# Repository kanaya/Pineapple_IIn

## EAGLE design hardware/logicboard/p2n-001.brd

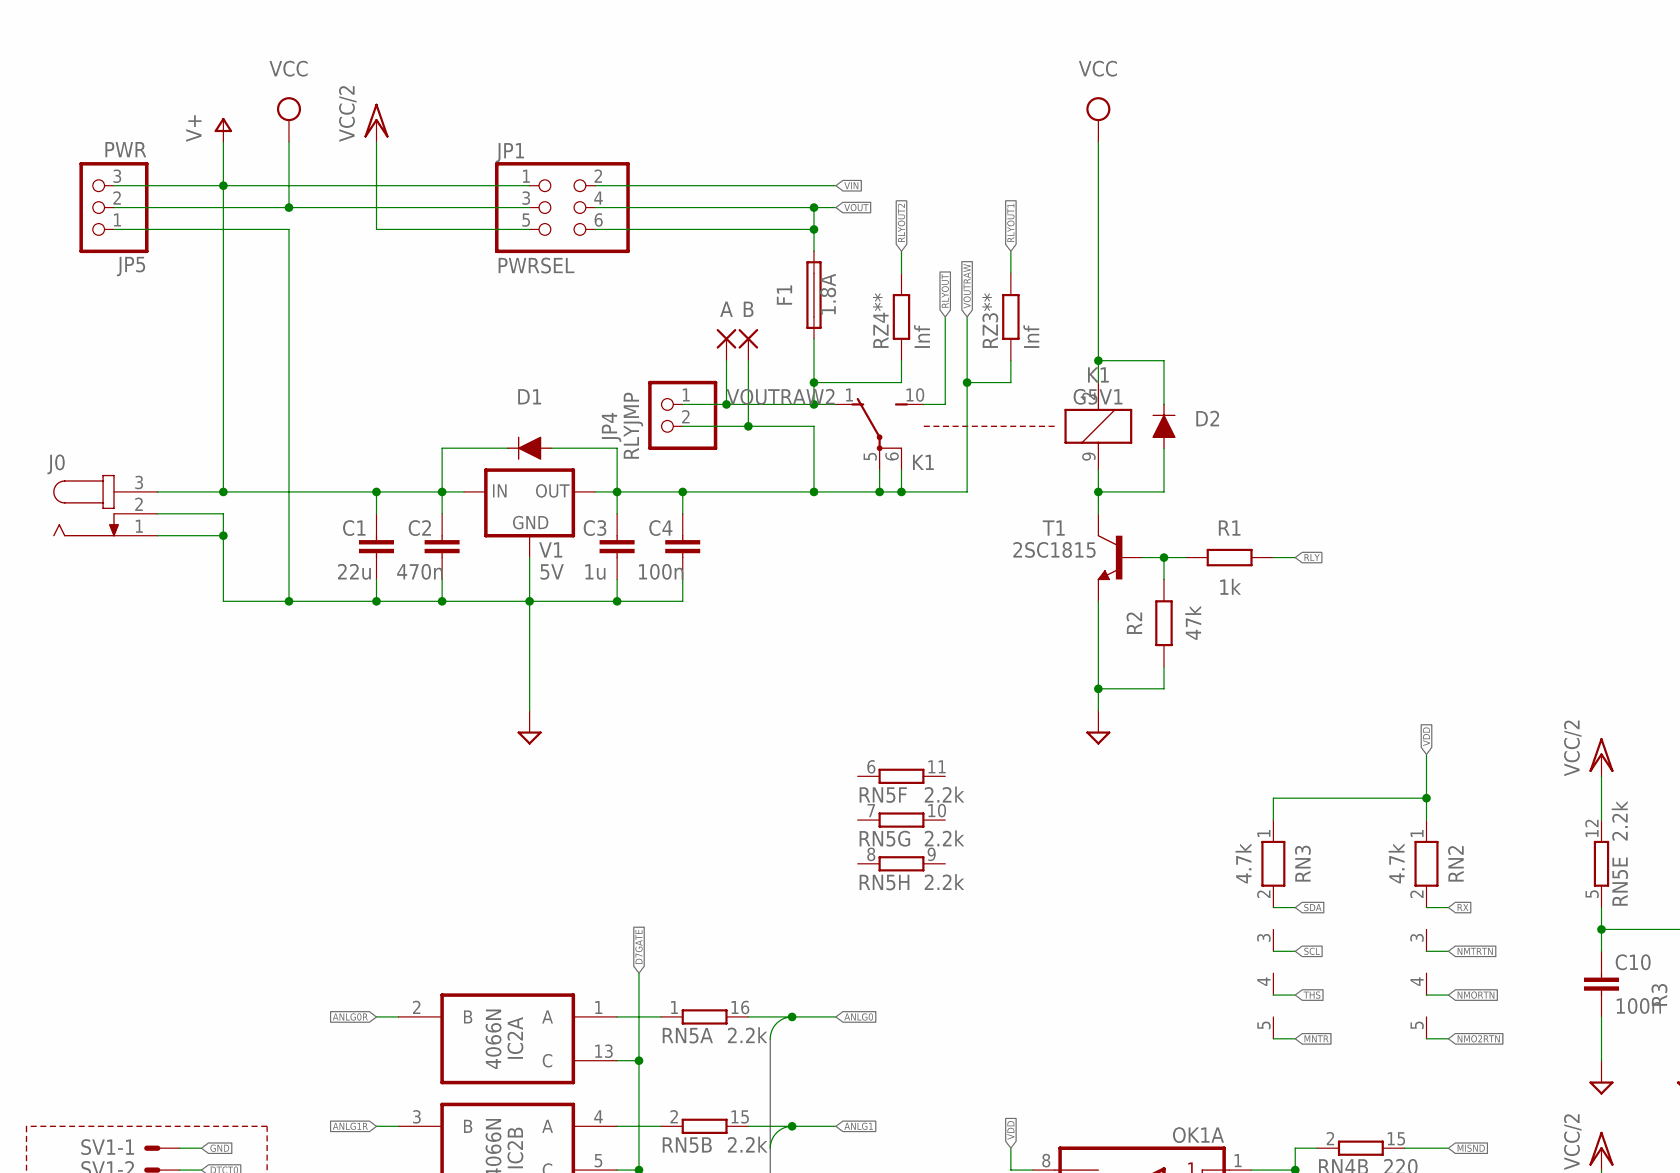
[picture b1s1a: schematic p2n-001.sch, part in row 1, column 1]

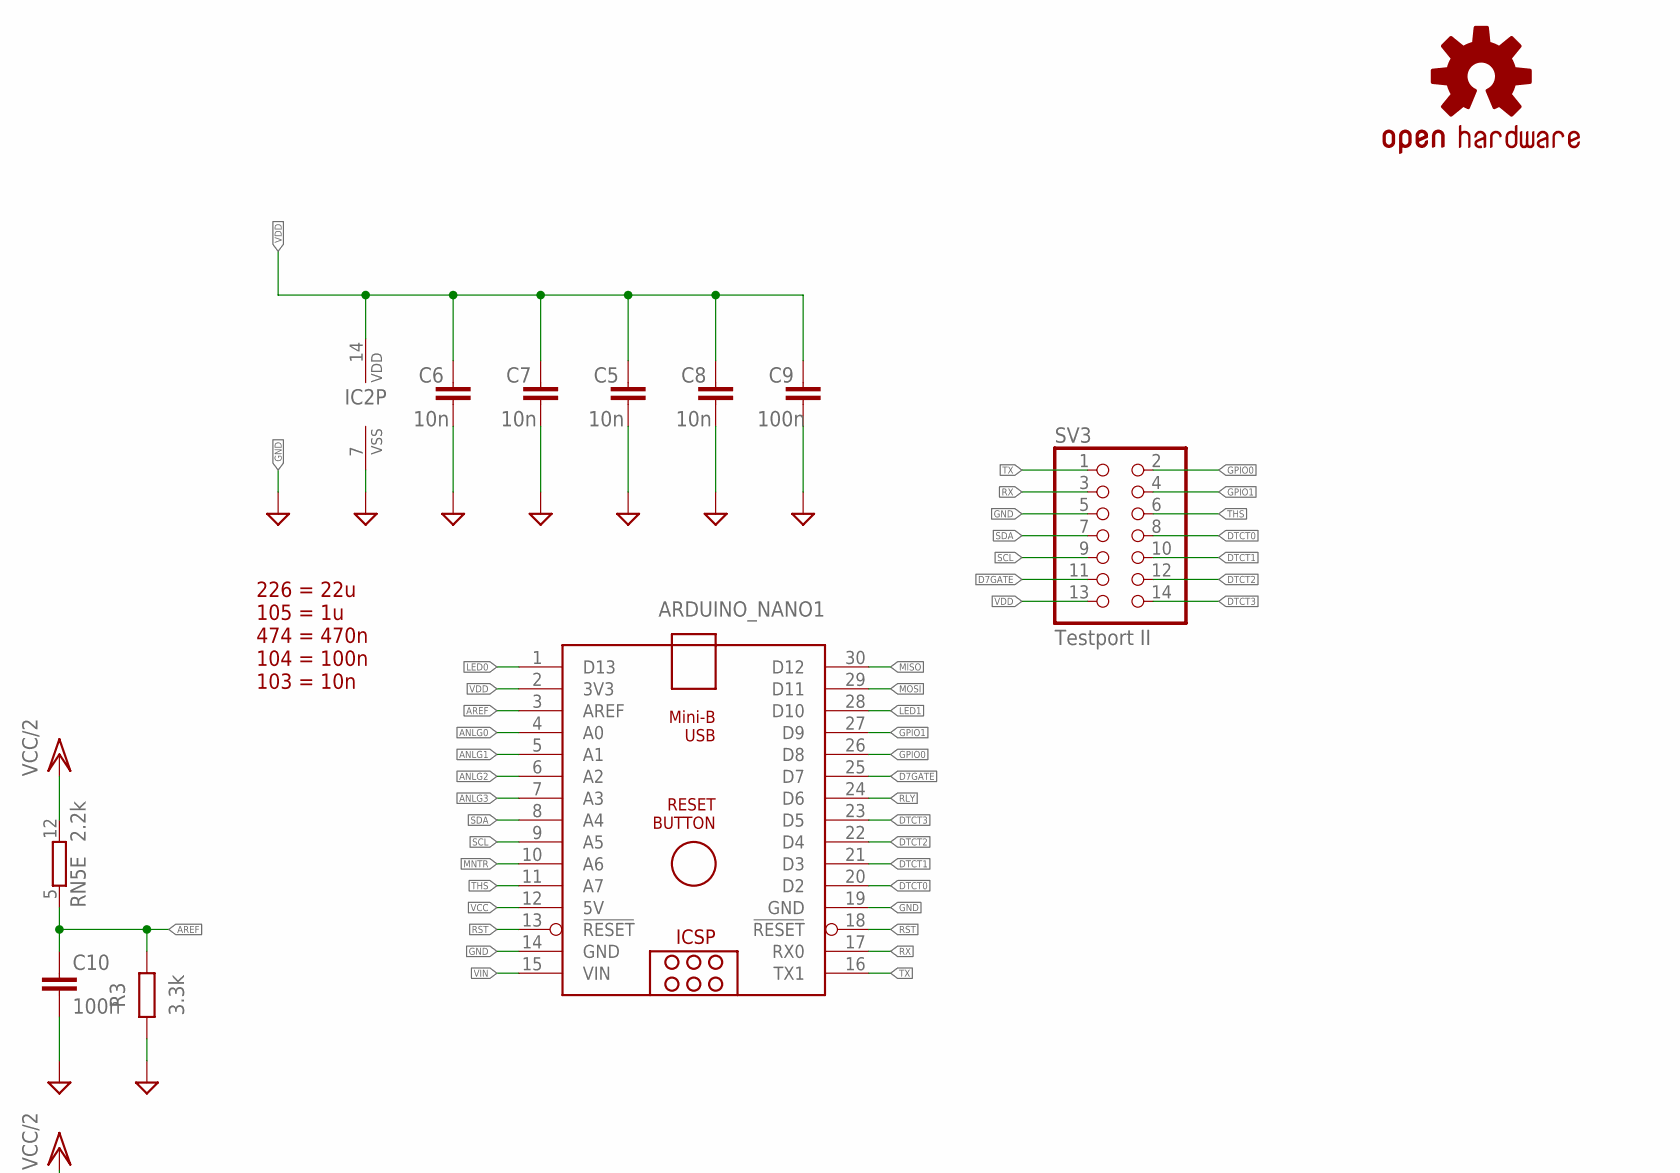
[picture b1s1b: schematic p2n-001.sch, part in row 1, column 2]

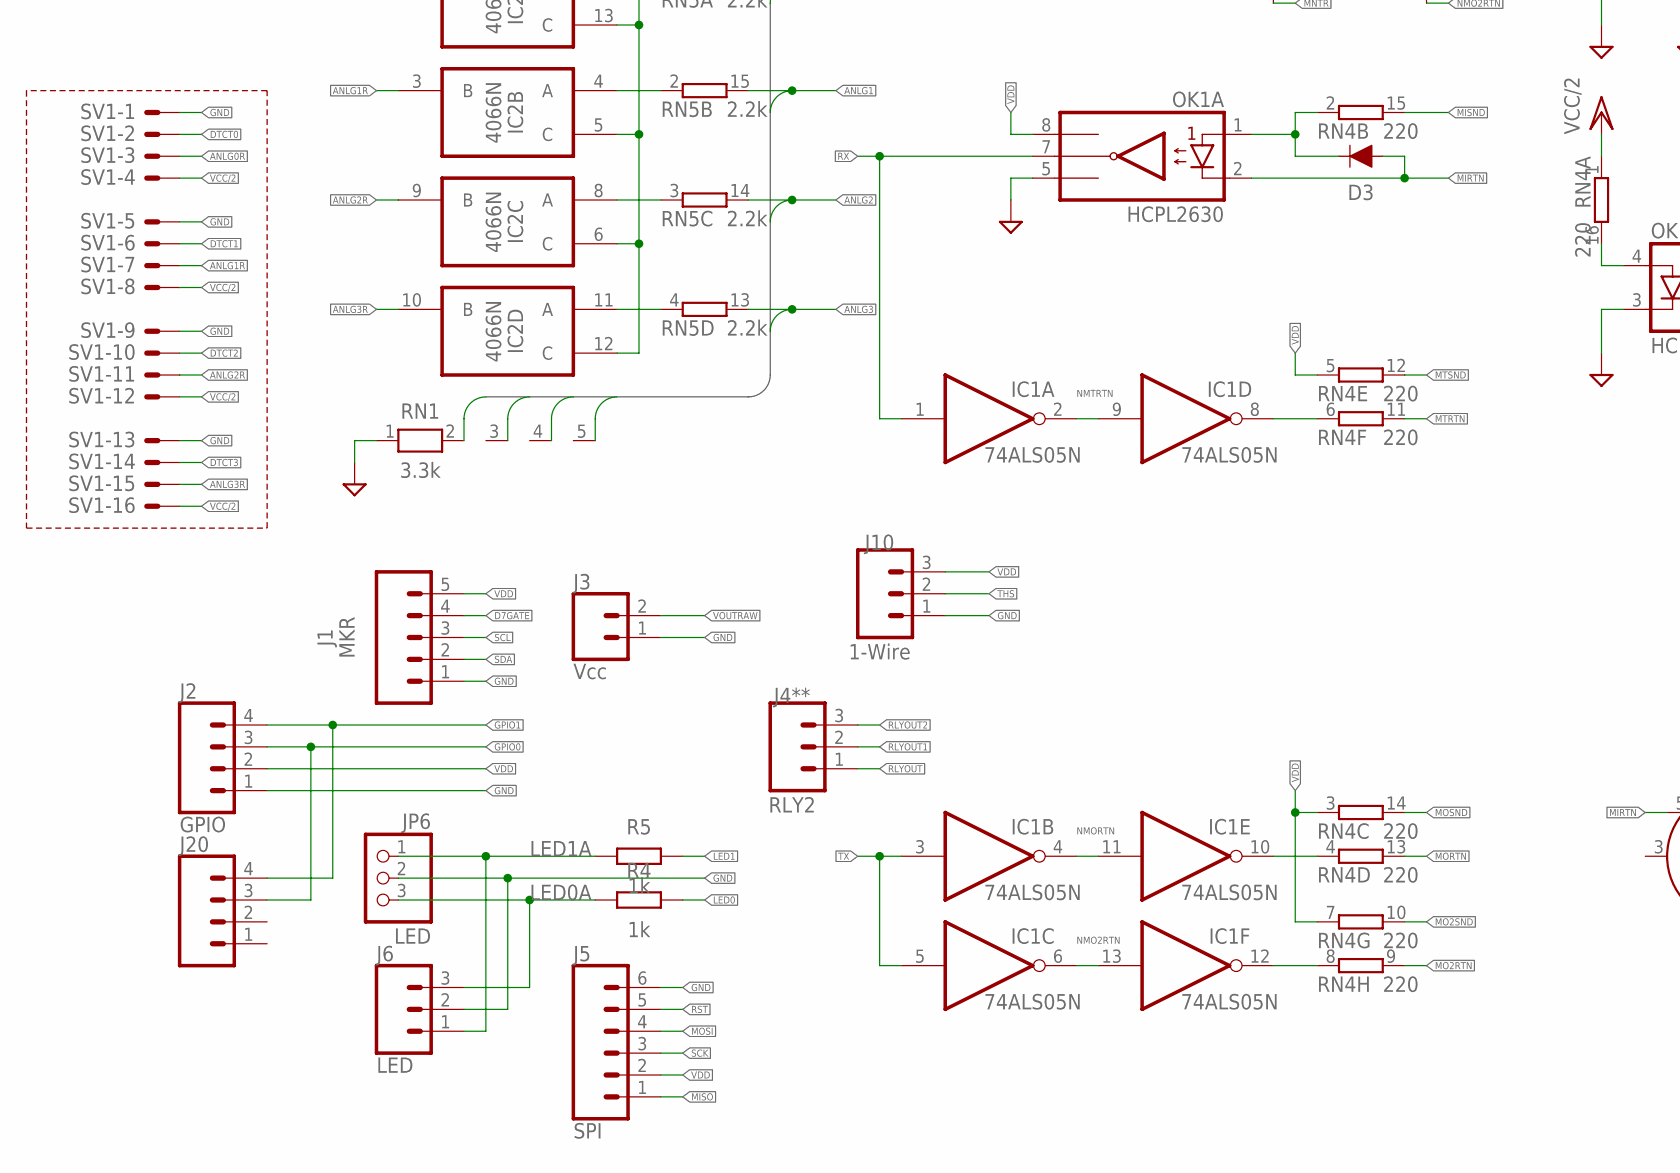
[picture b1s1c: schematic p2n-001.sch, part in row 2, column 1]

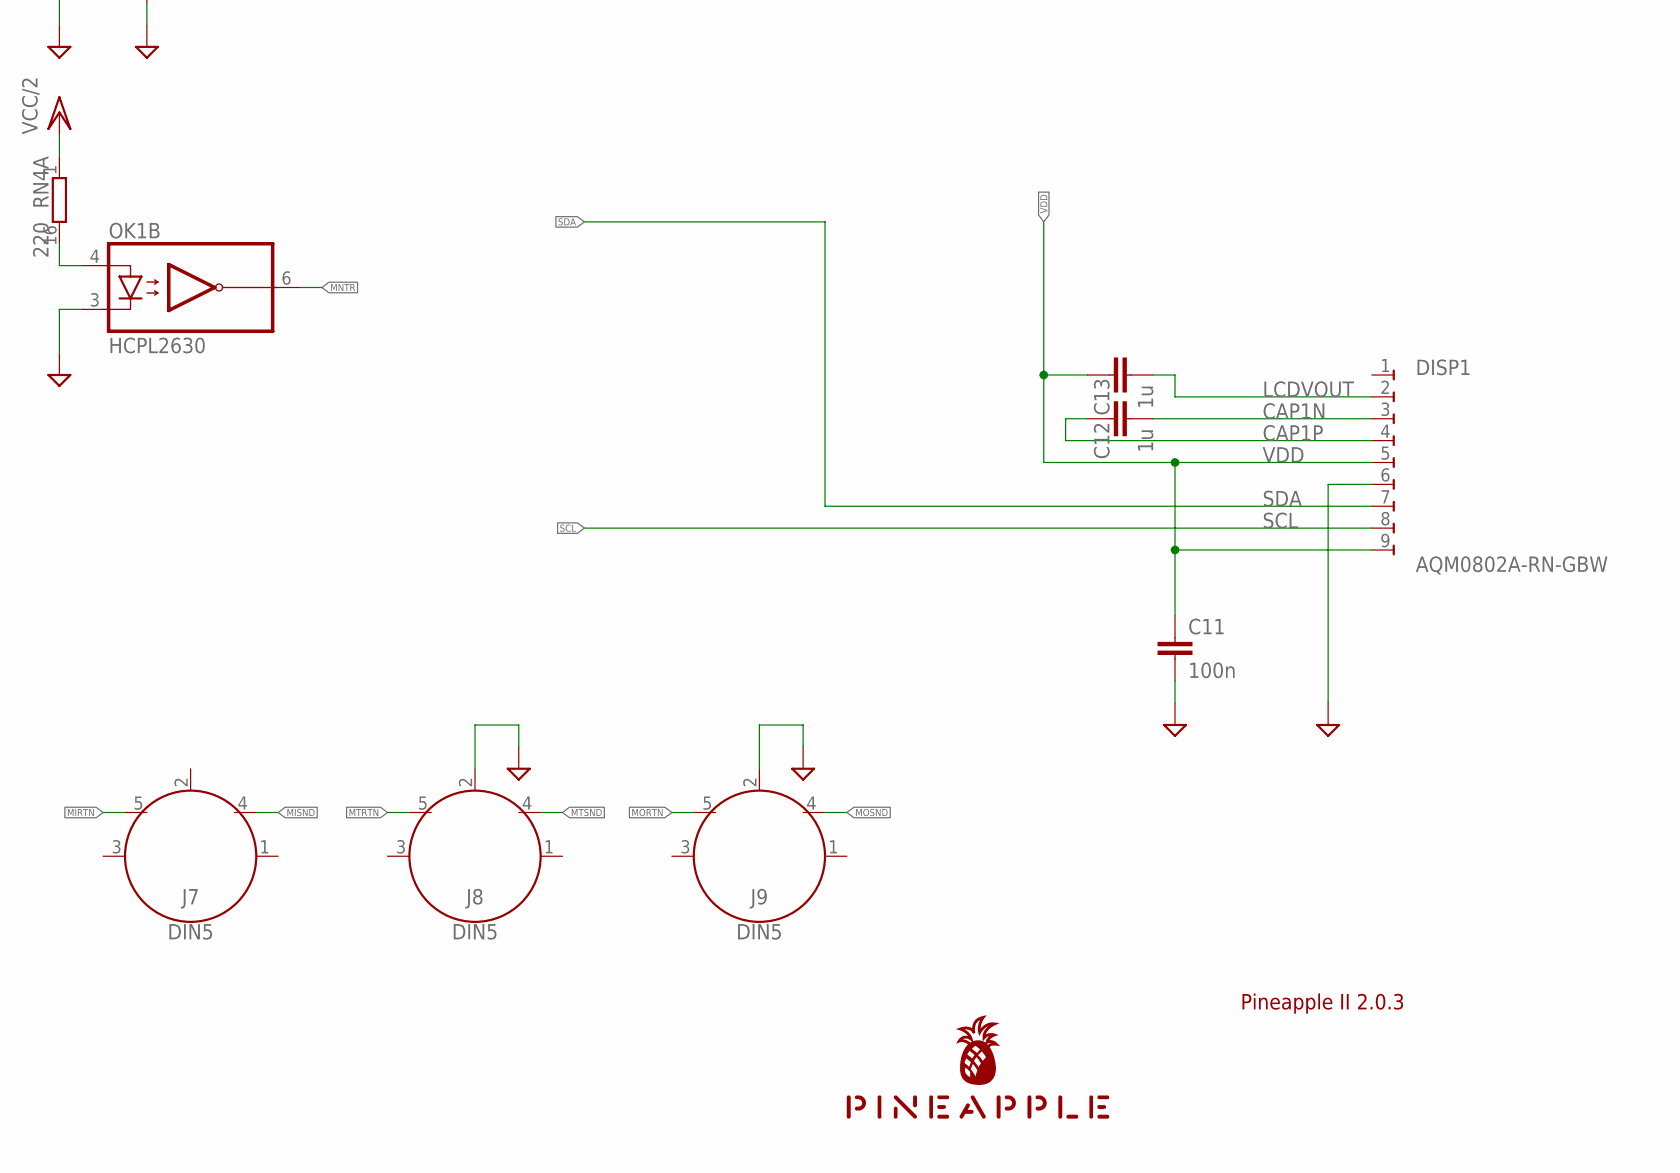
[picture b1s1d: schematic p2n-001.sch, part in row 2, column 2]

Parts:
A: SMD2; SMD1,27-2,54
ARDUINO_NANO1: ARDUINO_NANO
B: SMD2; SMD1,27-2,54
C1: 22u; C025-050X050
C2: 470n; C050-024X044
C3, C12, C13: 1u; C050-024X044
C4, C9, C10, C11: 100n; C025-024X044
C5, C6, C7, C8: 10n; C025-024X044
D1, D2, D3: DIODE-1N4148
DISP1: AQM0802A-RN-GBW; AQM0802A-RN-GBW-FOOTPRINT
F1: 1.8A; TE5
IC1: 74ALS05N; DIL14
IC2: 4066N; DIL14
J0: JACK-PLUG0; SPC4077
J1: MKR; JST-5-PTH
J2: GPIO; JST-4-PTH
J3: Vcc; JST-2-PTH
J4**: RLY2; JST-3-PTH-NS
J5: SPI; 1X06_1.27MM
J6: LED; JST-3-PTH-VERT
J7, J8, J9: DIN5; DIN5-RA-PTH
J10: 1-Wire; JST-3-PTH-VERT
J20: CONN_041.27MM; 1X04_1.27MM
JP1: PWRSEL; 2X03
JP4: RLYJMP; 1X02
JP5: PWR; 1X03
JP6: LED; 1X03
K1: G5V1
LOGO1: OSHW-LOGOS-COPPER; OSHW-LOGO-S_COPPER
OK1: HCPL2630; DIL08
R1, R4, R5: 1k; 0204/5
R2: 47k; 0204/5
R3: 3.3k; 0204/5
RN1: 3.3k; RN-5
RN2, RN3: 4.7k; RN-5
RN4: 220; DIL16
RN5: 2.2k; DIL16
RZ3**, RZ4**: Inf; M2012
SV1: ML16LE; ML16L
SV3: Testport II; 2X07
T1: 2SC1815; TO92-ECB
U$1: PINEAPPLE450_SILK
V1: 5V; 78XXL

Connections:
ANLG0: ARDUINO_NANO1.4 (A0), RN1.2, RN5.16 (2)
ANLG0R: IC2.2 (B), SV1.3
ANLG1: ARDUINO_NANO1.5 (A1), RN1.3, RN5.15 (2)
ANLG1R: IC2.3 (B), SV1.7
ANLG2: ARDUINO_NANO1.6 (A2), RN1.4, RN5.14 (2)
ANLG2R: IC2.9 (B), SV1.11
ANLG3: ARDUINO_NANO1.7 (A3), RN1.5, RN5.13 (2)
ANLG3R: IC2.10 (B), SV1.15
AREF: ARDUINO_NANO1.3 (AREF), C10.1, R3.2, RN5.5 (1)
CAP1N: C12.2, DISP1.3
CAP1P: C12.1, DISP1.4
D7GATE: ARDUINO_NANO1.25 (D7), IC2.5 (C), IC2.6 (C), IC2.12 (C), IC2.13 (C), J1.4, SV3.11
DTCT0: ARDUINO_NANO1.20 (D2), SV1.2, SV3.8
DTCT1: ARDUINO_NANO1.21 (D3), SV1.6, SV3.10
DTCT2: ARDUINO_NANO1.22 (D4), SV1.10, SV3.12
DTCT3: ARDUINO_NANO1.23 (D5), SV1.14, SV3.14
GND: ARDUINO_NANO1.14 (GND), ARDUINO_NANO1.19 (GND), C1.2, C2.2, C3.2, C4.2, C5.2, C6.2, C7.2, C8.2, C9.2, C10.2, C11.2, DISP1.6, IC1.7 (GND), IC2.7 (VSS), J0.1, J0.2, J1.1, J2.1, J3.1, J5.6, J6.2, J8.2, J9.2, J10.1, JP5.1, JP6.2, OK1.3 (C2), OK1.5 (GND), R2.1, R3.1, RN1.1, SV1.1, SV1.5, SV1.9, SV1.13, SV3.5, T1.E, V1.GND
GPIO0: ARDUINO_NANO1.26 (D8), J2.3, J20.3, SV3.2
GPIO1: ARDUINO_NANO1.27 (D9), J2.4, J20.4, SV3.4
LCDVOUT: C13.2, DISP1.2
LED0: ARDUINO_NANO1.1 (D13), R4.2
LED0A: J6.3, JP6.3, R4.1
LED1: ARDUINO_NANO1.28 (D10), R5.2
LED1A: J6.1, JP6.1, R5.1
MIDIINSND: D3.C, OK1.1 (A1), RN4.2 (1)
MIRTN: D3.A, J7.5, OK1.2 (C1)
MISND: J7.4, RN4.15 (2)
MISO: ARDUINO_NANO1.30 (D12), J5.1
MNTR: ARDUINO_NANO1.10 (A6), OK1.6 (VO2), RN3.5
MNTRA: OK1.4 (A2), RN4.16 (2)
MO2RTN: RN4.9 (2)
MO2RTNRAW: IC1.12 (O), RN4.8 (1)
MO2SND: RN4.10 (2)
MORTN: J9.5, RN4.13 (2)
MORTNRAW: IC1.10 (O), RN4.4 (1)
MOSI: ARDUINO_NANO1.29 (D11), J5.4
MOSND: J9.4, RN4.14 (2)
MTRTN: J8.5, RN4.11 (2)
MTRTNRAW: IC1.8 (O), RN4.6 (1)
MTSND: J8.4, RN4.12 (2)
unnamed: IC2.1 (A), RN5.1
unnamed: IC2.4 (A), RN5.2 (1)
unnamed: IC2.8 (A), RN5.3 (1)
unnamed: IC2.11 (A), RN5.4 (1)
NMO2RTN: IC1.6 (O), IC1.13 (I), RN2.5
NMORTN: IC1.4 (O), IC1.11 (I), RN2.4
NMTRTN: IC1.2 (O), IC1.9 (I), RN2.3
RLY: ARDUINO_NANO1.24 (D6), R1.2
RLYDRV: R1.1, R2.2, T1.B
RLYOUT: J4**.1, K1.10 (S)
RLYOUT1: J4**.2, RZ3**.2
RLYOUT2: J4**.3, RZ4**.2
RLYSNK: D2.A, K1.9 (2), T1.C
RST: ARDUINO_NANO1.13 (!RESET), ARDUINO_NANO1.18 (!RESET), J5.5
RX: ARDUINO_NANO1.17 (RX0), IC1.1 (I), OK1.7 (VO1), RN2.2, SV3.3
SCK: J5.3
SCL: ARDUINO_NANO1.9 (A5), DISP1.8, J1.3, RN3.3, SV3.9
SDA: ARDUINO_NANO1.8 (A4), DISP1.7, J1.2, RN3.2, SV3.7
THS: ARDUINO_NANO1.11 (A7), J10.2, RN3.4, SV3.6
TX: ARDUINO_NANO1.16 (TX1), IC1.3 (I), IC1.5 (I), SV3.1
V+: C1.1, C2.1, D1.C, J0.3, JP1.1, JP5.3, V1.IN
VCC: ARDUINO_NANO1.12 (5V), D2.C, IC1.14 (VCC), JP1.3, JP5.2, K1.2 (1)
VCC/2: JP1.5, RN4.1, RN5.12 (2), SV1.4, SV1.8, SV1.12, SV1.16
VDD: ARDUINO_NANO1.2 (3V3), C5.1, C6.1, C7.1, C8.1, C9.1, C11.1, C13.1, DISP1.5, DISP1.9, IC2.14 (VDD), J1.5, J2.2, J5.2, J10.3, OK1.8 (VCC), RN2.1, RN3.1, RN4.3 (1), RN4.5 (1), RN4.7 (1), SV3.13
VIN: ARDUINO_NANO1.15 (VIN), JP1.2
VOUT: F1.2, JP1.4, JP1.6
VOUTRAW: B.1, C3.1, C4.1, D1.A, J3.2, JP4.2, K1.5, K1.6, RZ3**.1, V1.OUT
VOUTRAW2: A.1, F1.1, JP4.1, K1.1 (O), RZ4**.1

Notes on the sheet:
Pineapple II 2.0.3
226 = 22u 105 = 1u 474 = 470n 104 = 100n 103 = 10n

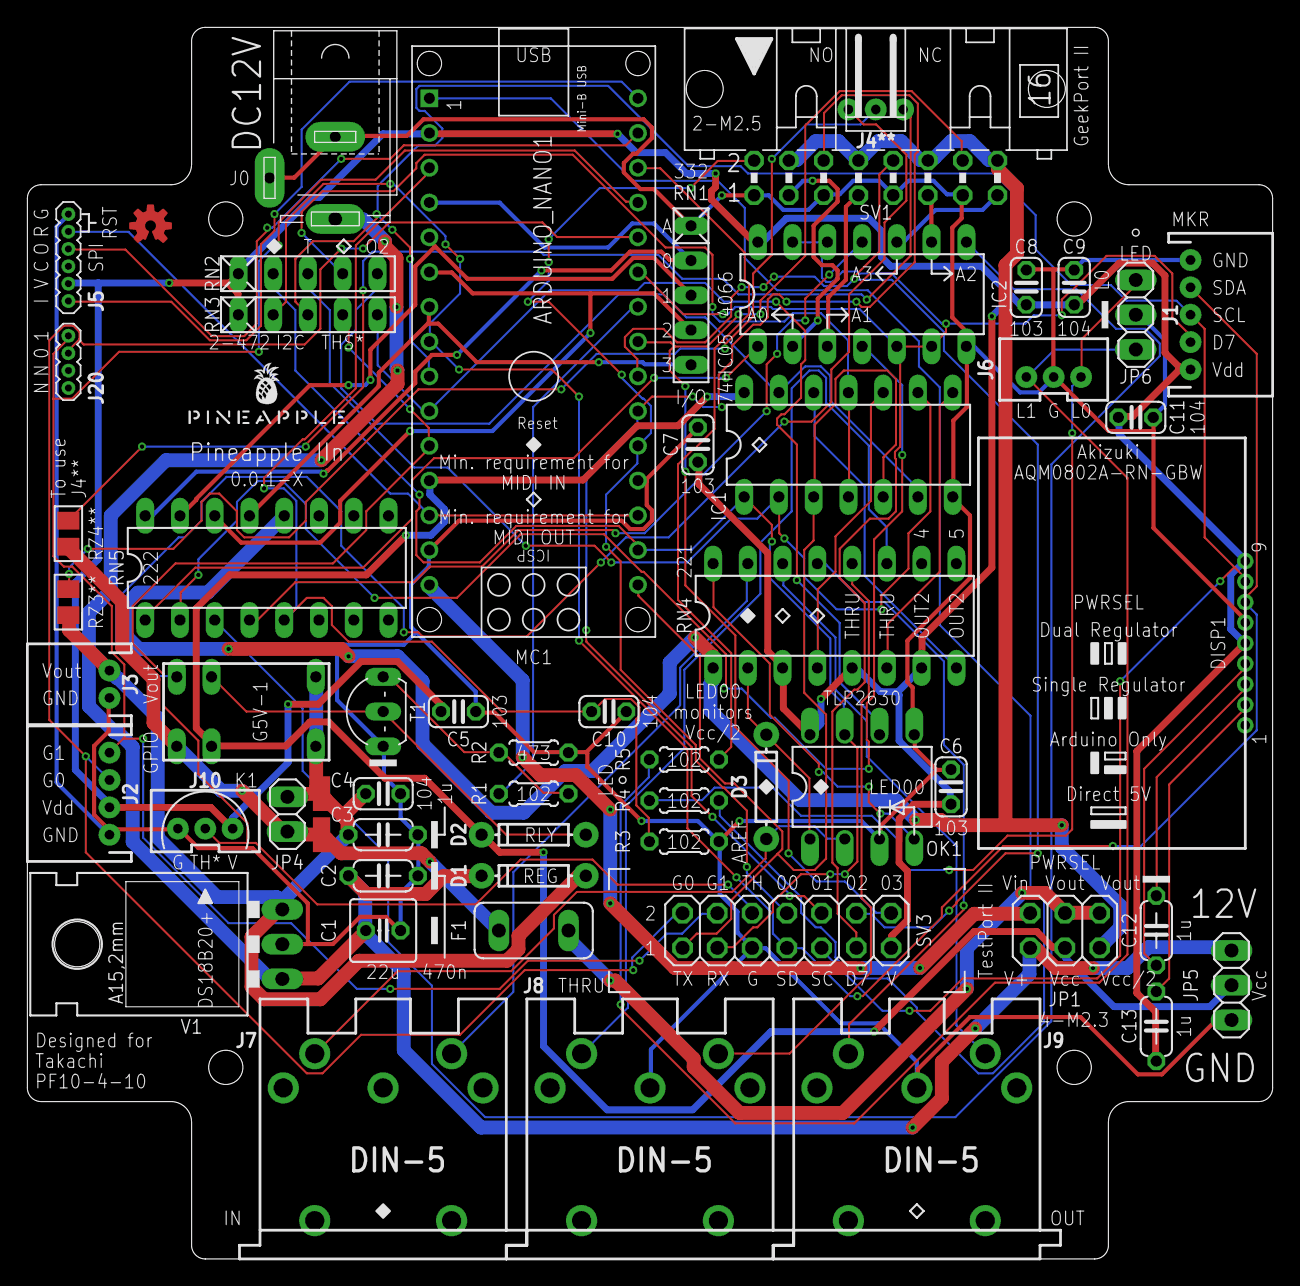
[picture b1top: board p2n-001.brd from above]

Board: 2 copper layers, 91.0 x 90.0 mm, 59 parts (0 on the bottom side), 65 nets.

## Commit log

2022-09-19 Initial commit. (Imported from Pineapple IIb.)
2022-09-19 Trying to install Nano.
2022-09-19 First try.
2022-09-19 Silk.

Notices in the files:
parts and their libraries:
SparkFun-DiscreteSemi: Licensing: Creative Commons ShareAlike 4.0 International - https://creativecommons.org/licenses/by-sa/4.0
